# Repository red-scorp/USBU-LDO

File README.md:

# USBU-LDO Project

The **USBU-LDO** project is a aimed to create low-cost DIY board with microUSB with LDO power supply.

## USBU-LDO Board

The **USBU-LDO** is simple board that provides a microUSB connector and a low-dropout voltage regulator (LDO) to power a small device from a microUSB power source. The board is designed to be as small as possible and to be used in a variety of applications where a small, low-cost, and easy-to-use power supply is needed.

Current design is based on the [LM1117](https://www.ti.com/lit/ds/symlink/lm1117.pdf) LDO voltage regulator, which can provide up to 1A of output current at 3.3V. However, the board can be easily modified to use a different LDO voltage regulator if needed.

Preview:

You can view the [Schematics in PDF format](doc/USBU-LDO.pdf) for detailed information.

STEP 3D file is available [here](doc/USBU-LDO.step).

Features:

- MicroUSB connector for 5V power delivery
- 3.3V LDO voltage regulator up to 1A output current
- LED power indicator

CAM files, as well as the BOM and CPL files for JLCPCB and NextPCB, are available.

## Version History

### v1.1

- Improved microUSB connector footprint to produce in NextPCB

### v1.0

Initial release.

## Links

- TBD

## How to Help

Your contributions as code, resources, or finances are welcome! Please contact me directly via email at andriy.golovnya@gmail.com or through my [GitHub profile](https://github.com/red-scorp).

If you'd like to make a financial contribution, you can donate via [PayPal](http://paypal.me/redscorp) or [Ko-Fi](http://ko-fi.com/redscorp). Your support is greatly appreciated.

Thanks in advance!

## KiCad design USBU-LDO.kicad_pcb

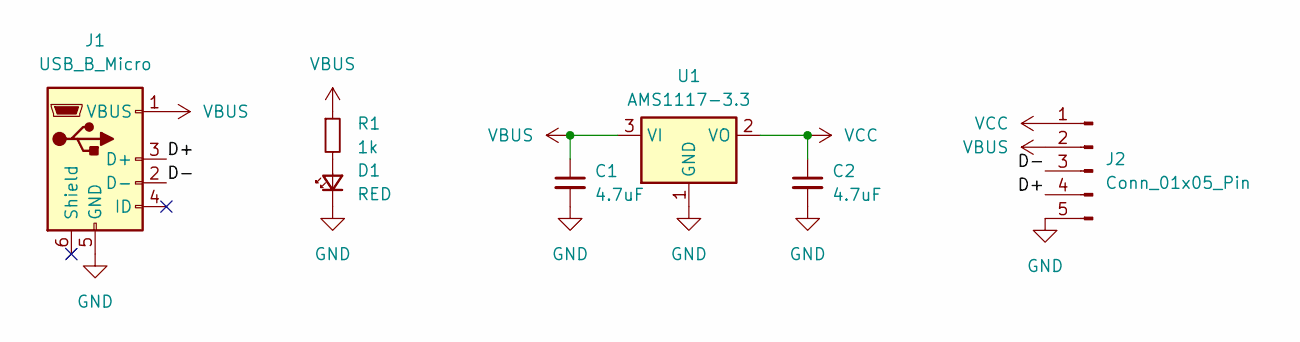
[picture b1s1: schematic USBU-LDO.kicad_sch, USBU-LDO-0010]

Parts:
C1, C2: 4.7uF; C_0805_2012Metric
D1: RED; LED_0603_1608Metric
J1: USB_B_Micro; USB_Micro-B_Molex_47346-0001
J2: Conn_01x05_Pin; PinHeader_1x05_P2.54mm_Vertical
R1: 1k; R_0402_1005Metric
U1: AMS1117-3.3; SOT-223-3_TabPin2

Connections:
/D+: J1.3 (D+), J2.4
/D-: J1.2 (D-), J2.3
GND: C1.2, C2.2, D1.1 (K), J1.5 (GND), J2.5, U1.1 (GND)
unnamed: D1.2 (A), R1.2
VBUS: C1.1, J1.1 (VBUS), J2.2, R1.1, U1.3 (VI)
VCC: C2.1, J2.1, U1.2 (VO)

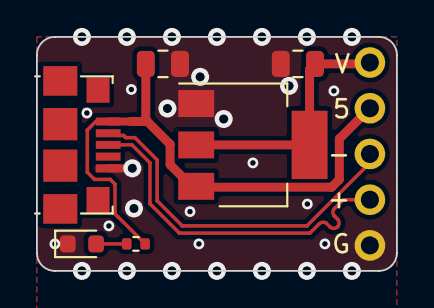
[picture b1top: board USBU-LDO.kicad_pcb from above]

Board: 2 copper layers, 20.0 x 13.0 mm, 7 parts (0 on the bottom side), 6 nets.

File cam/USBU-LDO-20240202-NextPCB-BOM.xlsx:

Designator | Qty | Manufacturer Part Number | Customer Supply | Customer Remark
C2,C1 | 2 | CL21A475KAQNNNE | -- | 4.7uF
R1 | 1 | 0402WGF1001TCE | -- | 1k
D1 | 1 | KT-0603R | -- | RED
U1 | 1 | AMS1117-3.3 | -- | AMS1117-3.3
J1 | 1 | 920-D62A2021S10104 | -- | USB_B_Micro

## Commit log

2024-01-31 First board design
2024-02-01 Rounded board corners. Moved texts around.
2024-02-01 Renamed the board
2024-02-01 Added page descriptions
2024-02-01 Generated CAM files
2024-02-01 Generated PDF schematics
2024-02-01 Generated STEP 3D model
2024-02-02 Generated PNG preview
2024-02-02 Generated BOM and CPL files
2024-02-02 Added FUNDING file
2024-02-24 Added NextPCB CAM and BOM files
2024-02-26 Generated PnP files for NextPCB
2024-03-05 Improved microUSB footprint by NextPCB's request
2024-03-05 Generated CAM, BOM and CPL files
2024-03-05 Improved microUSB footprint a bit to not go too close to the LED
2024-03-10 Added README.md
